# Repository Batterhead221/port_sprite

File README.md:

# PORT_SPRITE

Compact USB-C to UART debug/programming interface for embedded hardware projects.

PORT_SPRITE is a reusable bench tool for custom PCB bring-up. It provides USB-C serial access, 3.3V UART logic, selectable target power output, activity LEDs, reset/boot controls, and labeled test points so new boards can be programmed, tested, and debugged without rebuilding the same support circuit every time.

> USB in. UART out. Tiny port familiar doing serial errands.

## Project Status

| Item | Value |
|---|---|
| Revision | V1 |
| Status | In layout / pre-fabrication review |
| EDA | KiCad |
| Board type | USB-C to UART debug interface |

## System Role

```text
Computer / USB-C
        ↓ USB 2.0
PORT_SPRITE / CP2102N
        ↓ UART / reset / boot / VOUT
Target microcontroller board
```

PORT_SPRITE is not the target application board. It is a reusable debug/programming helper for other embedded projects.

## Main Features

- USB-C device input
- CP2102N USB-to-UART bridge
- 3.3V UART logic
- Selectable target power output
  - 3.3V from onboard AP2112K regulator
  - 5V from fused USB VBUS
- Target debug header with GND, VOUT, TXD, RXD, CTS, RTS, RESET, and BOOT_LOW
- Manual RESET button for target board
- Manual BOOT_LOW button for ESP-style boot/GPIO0 workflows
- TX/RX activity LEDs
- Power LED
- USB data ESD protection
- VBUS sense divider for CP2102N
- Exposed test points for key nets

## What This Board Is For

PORT_SPRITE is meant to live on the bench and plug into future embedded projects.

Use it for:

- UART serial logging
- Firmware flashing workflows
- Testing custom target boards
- Bringing up new microcontroller projects
- Probing TX/RX/RTS/CTS/VOUT rails
- Powering small target boards from USB
- ESP-style BOOT/RESET programming workflows

## Key Specs

| Item | Value |
|---|---|
| USB-UART bridge | CP2102N-Axx-xQFN20 |
| USB connector | USB-C USB 2.0 receptacle |
| UART logic level | 3.3V |
| Target power output | Selectable 3.3V or fused USB 5V |
| Regulator | AP2112K-3.3 |
| USB ESD | TPD2EUSB30 or equivalent |
| Target header | 1x8 UART/debug header |
| Manual controls | RESET and BOOT_LOW buttons |
| Indicators | Power LED, TX LED, RX LED |
| Board role | USB-C UART/debug/programming helper |

## Important Electrical Behavior

### UART Logic Level

The UART signal pins use **3.3V logic**.

The `VOUT` selector can provide either 3.3V or 5V power to the target, but the UART logic does **not** become 5V logic.

```text
UART TX/RX/CTS/RTS logic level = 3.3V
VOUT selectable rail            = 3.3V or 5V
```

Do not connect PORT_SPRITE UART pins directly to a target that drives 5V logic unless level shifting or 5V tolerance is confirmed.

### VOUT Selector

The slide switch selects what voltage appears on the `VOUT` pin.

| Switch input | Source |
|---|---|
| `+3V3` | AP2112K 3.3V regulator output |
| `VBUS_5V` | Fused USB 5V rail |

`VOUT` is intended for small target boards only. Do not use it as a high-current supply.

### BOOT_LOW

`BOOT_LOW` is a pull-low boot control intended for ESP-style boot/GPIO0 workflows.

For STM32-style BOOT0, confirm the target board requirements before use. STM32 BOOT0 often expects pull-high behavior instead.

## Target Header Pinout

| Pin | Signal | Direction / Purpose |
|---:|---|---|
| 1 | GND | Ground reference |
| 2 | VOUT | Selected target power output |
| 3 | TXD_TO_TARGET_RX | PORT_SPRITE TXD to target RX |
| 4 | RXD_FROM_TARGET_TX | Target TX to PORT_SPRITE RXD |
| 5 | CTS | CP2102N CTS |
| 6 | RTS | CP2102N RTS |
| 7 | RESET | Target reset, button pulls low |
| 8 | BOOT_LOW | Target boot/GPIO0, button pulls low |

## Typical Target Wiring

UART wiring crosses TX and RX:

```text
PORT_SPRITE TXD_TO_TARGET_RX  → target RX
PORT_SPRITE RXD_FROM_TARGET_TX ← target TX
PORT_SPRITE GND               ↔ target GND
PORT_SPRITE VOUT              → optional target power input
```

RESET and BOOT_LOW are optional and depend on the target board design.

## Test Points

| Test Point | Net | Purpose |
|---|---|---|
| TP1 | GND | Ground reference |
| TP2 | VBUS_5V | USB 5V rail check |
| TP3 | +3V3 | 3.3V regulator output check |
| TP4 | RXD_FROM_TARGET_TX | UART RX probe point |
| TP5 | TXD_TO_TARGET_RX | UART TX probe point |
| TP6 | CTS | Flow-control probe point |
| TP7 | RTS | Flow-control / control probe point |
| TP8 | VOUT | Selected target output voltage |

## Main Components

| Ref | Part | Notes |
|---|---|---|
| U1 | CP2102N-Axx-xQFN20 | USB-to-UART bridge |
| U2 | TPD2EUSB30 or equivalent | USB D+/D- ESD protection |
| U3 | AP2112K-3.3 | 3.3V LDO regulator |
| J1 | USB-C USB 2.0 receptacle | Device/sink input |
| J2 | 1x8 target debug header | UART/debug interface |
| SW1 | SPDT slide switch | Selects VOUT source |
| SW2 | RESET button | Pulls target RESET low |
| SW3 | BOOT button | Pulls BOOT_LOW low |

## Power Architecture

```text
USB-C VBUS
      ↓
fuse / protection
      ↓
VBUS_5V rail
      ↓
AP2112K-3.3 regulator → +3V3
      ↓
VOUT selector chooses +3V3 or VBUS_5V
      ↓
target VOUT pin
```

## Bring-Up Checklist

Before plugging into a computer:

- [ ] Inspect USB-C connector solder joints.
- [ ] Inspect CP2102N orientation.
- [ ] Confirm no solder bridges on QFN pins.
- [ ] Check continuity between all GND points.
- [ ] Confirm `VBUS_5V` is not shorted to GND.
- [ ] Confirm `+3V3` is not shorted to GND.
- [ ] Confirm `VOUT` is not shorted to GND.
- [ ] Confirm USB D+ and D- are not shorted together.
- [ ] Confirm USB D+ and D- are not shorted to GND or VBUS.

Power checks:

- [ ] Plug into a current-limited USB source or USB power meter first.
- [ ] Measure `VBUS_5V`.
- [ ] Measure `+3V3`.
- [ ] Toggle VOUT selector and measure `VOUT` in both positions.
- [ ] Confirm PWR LED behavior.

USB checks:

- [ ] Confirm the board enumerates as a CP210x USB-to-UART device.
- [ ] Confirm TX/RX LEDs behave during serial activity.
- [ ] Perform loopback test between TXD and RXD.

## Loopback Test

Connect:

```text
TXD_TO_TARGET_RX ↔ RXD_FROM_TARGET_TX
```

Open a serial terminal. Any typed characters should echo back.

Suggested settings:

```text
Baud: 115200
Data: 8
Parity: none
Stop: 1
Flow control: none
```

## Design Notes

- Label TX/RX from PORT_SPRITE's point of view.
- UART wiring crosses TX to RX and RX to TX.
- Always share GND with the target board.
- Keep USB D+ and D- short and clean.
- Keep connector labels readable for fast bench use.
- Do not assume every target board is 5V tolerant.
- Treat VOUT as a convenience rail, not a high-current bench supply.

## Notes For Future Revision

Potential V2 ideas:

- Add true auto-reset/auto-boot support with DTR/RTS using a USB-UART bridge/package that exposes DTR.
- Add 1.8V logic support.
- Add target voltage sensing.
- Add USB isolation.
- Add current limiting or current measurement on VOUT.
- Add alternate pinout adapter cables.

## Repository Output Images

Expected image paths for GitHub README rendering:

```text
Outputs/
  IMG/
    3D-T.png
    3D-B.png
    SCHEMATIC.png
    L1-SIG.png
    L2-GND.png
```

## Safety / Design Note

PORT_SPRITE is a low-voltage debug/helper PCB. Verify UART voltage levels, shared ground, selected VOUT voltage, and target pin direction before connecting it to another project.

Designed & engineered by Brandon Shelly

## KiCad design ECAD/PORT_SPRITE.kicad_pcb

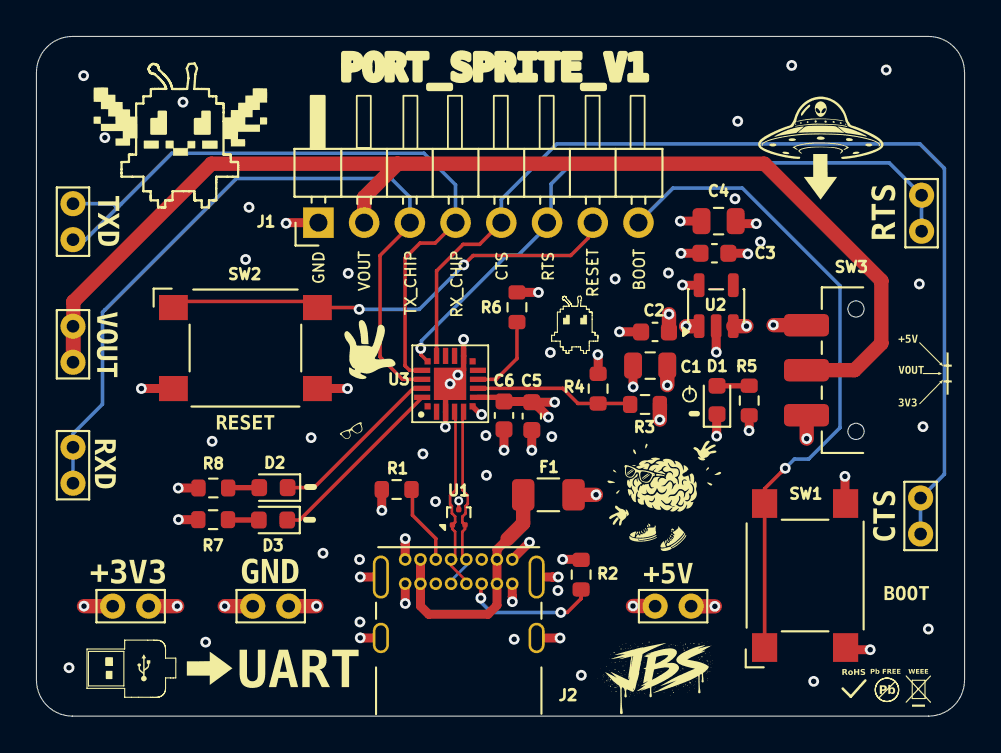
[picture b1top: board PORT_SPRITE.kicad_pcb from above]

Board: 4 copper layers, 51.6 x 37.8 mm, 34 parts (0 on the bottom side), 22 nets.

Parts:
C1, C4: 10U; C_0805_2012Metric
C2, C3, C6: 100NF; C_0603_1608Metric
C5: 1U; C_0603_1608Metric
D1: PWR (RED); LED_0603_1608Metric
D2: RX (BLUE); LED_0603_1608Metric
D3: TX (YELLOW); LED_0603_1608Metric
F1: 500mA; Fuse_1206_3216Metric
J1: UART_TARGET_HEADER; PinHeader_1x08_P2.54mm_Horizontal
J2: USB_C_Receptacle_USB2.0_14P; USB_C_Receptacle_GCT_USB4085
R1, R2: 5.1K; R_0603
R3: 22.1K; R_0603
R4: 47.5K; R_0603
R5, R7, R8: 1K; R_0603
R6: 10K; R_0603
SW1: BOOT_LOW_BTN; SW_SPST_Omron_B3FS-100xP
SW2: RESET_BTN; SW_SPST_Omron_B3FS-100xP
SW3: SLIDE_SWITCH; SW_SPDT_CK_JS102011SAQN
TP1: VOUT; TestPoint_Bridge_Pitch2.0mm_Drill0.7mm
TP2: RTS; TestPoint_Bridge_Pitch2.0mm_Drill0.7mm
TP3: CTS; TestPoint_Bridge_Pitch2.0mm_Drill0.7mm
TP4: TXD; TestPoint_Bridge_Pitch2.0mm_Drill0.7mm
TP5: RXD; TestPoint_Bridge_Pitch2.0mm_Drill0.7mm
TP6: +3V3; TestPoint_Bridge_Pitch2.0mm_Drill0.7mm
TP7: +5V; TestPoint_Bridge_Pitch2.0mm_Drill0.7mm
TP8: GND; TestPoint_Bridge_Pitch2.0mm_Drill0.7mm
U1: TPD2EUSB30; Texas_DRT-3
U2: AP2112K-3.3; SOT-23-5
U3: CP2102N-Axx-xQFN20; WFQFN-20

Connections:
/+3V3: C3.1, C4.1, C5.1, C6.1, R5.1, R6.2, R7.1, R8.1, SW3.1 (A), TP6.1, U2.5 (VOUT), U3.6 (VDD), U3.7 (VREGIN)
/BOOT_LOW: J1.8, SW1.1
/CP2102_RESET: R6.1, U3.9 (~RST)
/CTS: J1.5, TP3.1, U3.15 (~CTS)
/PWR_LED: D1.2 (A), R5.2
/RESET: J1.7, SW2.1
/RTS: J1.6, TP2.1, U3.16 (~RTS)
/RXD_FROM_TARGET_TX: J1.4, TP5.1, U3.17 (RXD)
/RX_LED: D2.2 (A), R8.2
/TXD_TO_TARGET_RX: J1.3, TP4.1, U3.18 (TXD)
/TX_LED: D3.2 (A), R7.2
/USB_D+: J2.A6 (D+), J2.B6 (D+), U1.1 (D+), U3.4 (D+)
/USB_D-: J2.A7 (D-), J2.B7 (D-), U1.2 (D-), U3.5 (D-)
/VBUS_5V: C1.1, C2.1, F1.2, R3.1, SW3.3 (C), TP7.1, U2.1 (VIN), U2.3 (EN)
/VBUS_RAW: F1.1, J2.A4 (VBUS), J2.A9 (VBUS), J2.B4 (VBUS), J2.B9 (VBUS)
/VBUS_SENSE: R3.2, R4.2, U3.8 (VBUS)
/VOUT: J1.2, SW3.2 (B), TP1.1
GND: C1.2, C2.2, C3.2, C4.2, C5.2, C6.2, D1.1 (K), J1.1, J2.A1 (GND), J2.A12 (GND), J2.B1 (GND), J2.B12 (GND), J2.SH (SHIELD), R1.2, R2.2, R4.1, SW1.2, SW2.2, TP8.1, U1.3 (GND), U2.2 (GND), U3.3 (GND), U3.12 (GND), U3.21 (GND)
unnamed: D2.1 (K), U3.19 (~RXT/GPIO.3)
unnamed: D3.1 (K), U3.20 (~TXT/GPIO.2)
unnamed: J2.A5 (CC1), R1.1
unnamed: J2.B5 (CC2), R2.1

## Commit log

2026-05-13 Revised repo
2026-05-24 readme
